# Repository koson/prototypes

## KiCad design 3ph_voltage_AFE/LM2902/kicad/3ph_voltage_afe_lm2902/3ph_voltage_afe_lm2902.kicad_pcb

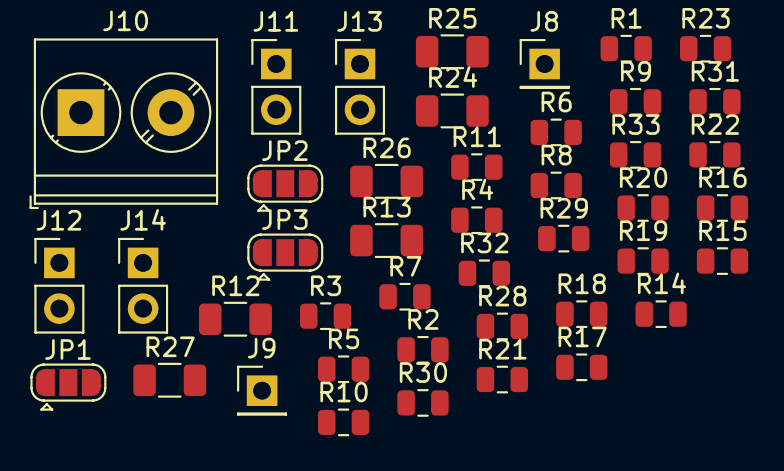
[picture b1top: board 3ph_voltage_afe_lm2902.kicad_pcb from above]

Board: 2 copper layers, 43 parts (0 on the bottom side), 29 nets, no tracks yet.

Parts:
J8: AC L; PinHeader_1x01_P2.54mm_Vertical
J9: AC N; PinHeader_1x01_P2.54mm_Vertical
J10: screw; TerminalBlock_Phoenix_PT-1,5-2-5.0-H_1x02_P5.00mm_Horizontal
J11: V_ref; PinHeader_1x02_P2.54mm_Vertical
J12: VDDA; PinHeader_1x02_P2.54mm_Vertical
J13: SIGNAL; PinHeader_1x02_P2.54mm_Vertical
J14: GNDA; PinHeader_1x02_P2.54mm_Vertical
JP1, JP2, JP3: Jumper_3_Bridged12; SolderJumper-3_P1.3mm_Open_RoundedPad1.0x1.5mm
R1, R2, R3, R4, R5, R6, R7, R8, R9, R15, R16, R17, R18, R19, R20, R21, R22, R23: 1M; R_0805_2012Metric
R10, R11, R28, R29, R30, R31: 240K; R_0805_2012Metric
R12, R13, R24, R25, R26, R27: R_div_ref; R_1206_3216Metric
R14, R32, R33: 15K; R_0805_2012Metric

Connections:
/AC_V_L: J8.1, J10.1, R1.1, R3.1, R4.1
/AC_V_N: J9.1, J10.2, R2.1, R5.1, R15.1
/GNDA: J14.1, J14.2, R13.1, R25.1, R27.1
/OUT_SIG: J13.1, J13.2, R14.2, R32.2, R33.2
/Reference_voltage: JP1.2, JP2.2, JP3.2, R10.2, R28.2, R30.2
/VDDA: J12.1, J12.2, R12.2, R24.2, R26.2
/V_div: JP1.1, JP2.1, JP3.1, R12.1, R13.2, R24.1, R25.2, R26.1, R27.2
/ext_ref: J11.1, J11.2, JP1.3, JP2.3, JP3.3
unnamed: R1.2, R16.1
unnamed: R4.2, R6.1
unnamed: R5.2, R7.1
unnamed: R6.2, R8.1
unnamed: R7.2, R9.1
unnamed: R8.2, R10.1
unnamed: R9.2, R11.1
unnamed: R11.2, R14.1
unnamed: R15.2, R19.1
unnamed: R16.2, R20.1
unnamed: R2.2, R17.1
unnamed: R17.2, R21.1
unnamed: R3.2, R18.1
unnamed: R18.2, R22.1
unnamed: R19.2, R23.1
unnamed: R20.2, R28.1
unnamed: R21.2, R29.1
unnamed: R22.2, R30.1
unnamed: R23.2, R31.1
unnamed: R29.2, R32.1
unnamed: R31.2, R33.1

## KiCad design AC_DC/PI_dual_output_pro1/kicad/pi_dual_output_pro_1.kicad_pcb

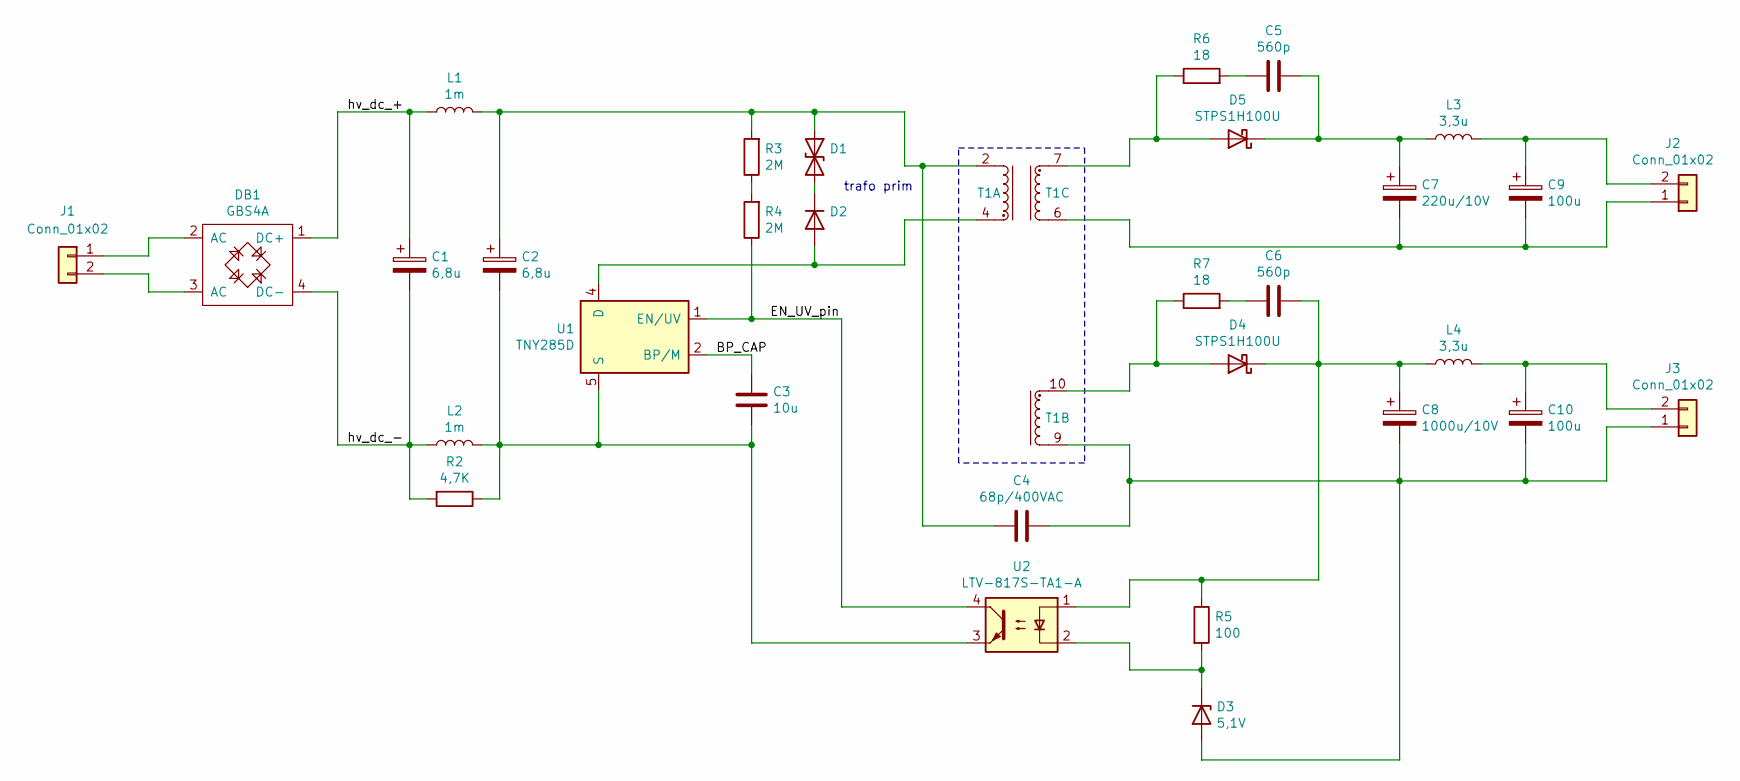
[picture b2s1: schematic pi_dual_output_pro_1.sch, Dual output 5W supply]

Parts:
C1, C2: 6,8u; CP_Radial_D10.0mm_P5.00mm
C3: 10u; C_0805_2012Metric
C4: 68p/400VAC; C_Disc_D5.0mm_W2.5mm_P5.00mm
C5, C6: 560p; C_0603_1608Metric
C7: 220u/10V; CP_Radial_D6.3mm_P2.50mm
C8: 1000u/10V; CP_Radial_D10.0mm_P5.00mm
C9, C10: 100u; CP_Radial_D5.0mm_P2.00mm
D1: SMAJ100A-13-F; D_SMA
D2: S1K; D_SMA
D3: 5,1V; D_SOD-123
D4, D5: STPS1H100U; D_SMB
DB1: GBS4A; Diode_Bridge_19.0x3.5x10.0mm_P5.0mm
J1, J2, J3: Conn_01x02; TerminalBlock_Phoenix_PT-1,5-2-5.0-H_1x02_P5.00mm_Horizontal
L1, L2: 1m; L_Radial_D8.7mm_P5.00mm_Fastron_07HCP
L3, L4: 3,3u; L_Radial_D6.0mm_P4.00mm
R2: 4,7K; R_0805_2012Metric
R3, R4: 2M; R_1206_3216Metric
R5: 100; R_0805_2012Metric
R6, R7: 18; R_0805_2012Metric
T1: EE13_Custom; EE13_Bobbin
U1: TNY285D; PowerIntegrations_SO-8C
U2: LTV-817S-TA1-A; SMDIP-4_W9.53mm

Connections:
/BP_CAP: C3.1, U1.2 (BP/M)
/EN_UV_pin: R4.1, U1.1 (EN/UV), U2.4
/hv_dc_+: C1.1, DB1.1 (DC+), L1.1
/hv_dc_-: C1.2, DB1.4 (DC-), L2.1, R2.2
unnamed: C2.1, C4.2, D1.1 (A1), L1.2, R3.2, T1.2
unnamed: C2.2, C3.2, L2.2, R2.1, U1.5 (S), U1.6 (S), U1.7 (S), U1.8 (S), U2.3
unnamed: C5.1, C7.1, D5.1 (K), L3.1
unnamed: C5.2, R6.2
unnamed: C6.1, C8.1, D4.1 (K), L4.1, R5.1, U2.1
unnamed: C6.2, R7.2
unnamed: C7.2, C9.2, J2.1, T1.6
unnamed: C9.1, J2.2, L3.2
unnamed: C10.1, J3.2, L4.2
unnamed: C4.1, C8.2, C10.2, D3.2 (A), J3.1, T1.9
unnamed: D1.2 (A2), D2.1 (K)
unnamed: D2.2 (A), T1.4, U1.4 (D)
unnamed: D3.1 (K), R5.2, U2.2
unnamed: D4.2 (A), R7.1, T1.10
unnamed: D5.2 (A), R6.1, T1.7
unnamed: DB1.2 (AC), J1.1
unnamed: DB1.3 (AC), J1.2
unnamed: R3.1, R4.2

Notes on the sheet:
trafo prim

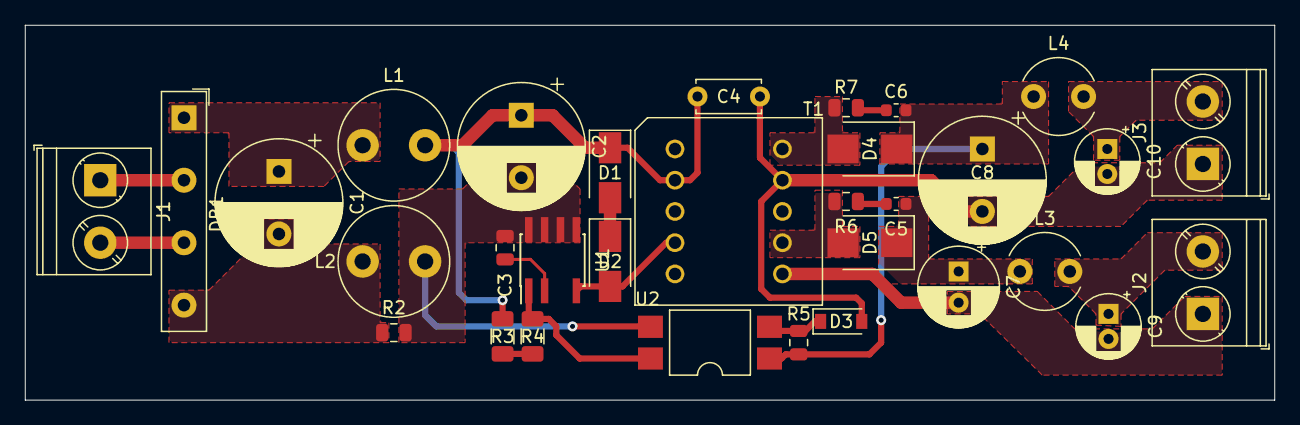
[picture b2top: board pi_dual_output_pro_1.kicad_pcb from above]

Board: 2 copper layers, 100.0 x 30.0 mm, 32 parts (0 on the bottom side), 22 nets.

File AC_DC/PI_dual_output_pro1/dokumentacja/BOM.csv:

Id;Oznaczenie;Obudowa;Iloæ;Oznaczenie;Dostawca;Numer artyku³u;PARKING / KOSZYK
1;R6,R7;R_0805_2012Metric;2;18;TME;0805S8J0180T5E;TAK
2;U2;SMDIP-4_W9.53mm;1;LTV-817S-TA1-A;TME; LTV-817S-TA1-B;TAK
3;DB1;Diode_Bridge_19.0x3.5x10.0mm_P5.0mm;1;GBS4A;TME; GBS4K ;TAK
4;T1;EE13_Bobbin;1;EE13_Custom;FERYSTER;TI-EE13-2X5V;-
6;C8;CP_Radial_D10.0mm_P5.00mm;1;1000u/10V;"TME
FARNELL";"ECA-1AHG102
EEUFS1A102";"TAK
TAK"
7;J3,J2,J1;TerminalBlock_Phoenix_PT-1,5-2-5.0-H_1x02_P5.00mm_Horizontal;3;Conn_01x02;-;-;-
8;D3;D_SOD-123;1;5,1V;TME;BZT52C5V1-13-F;TAK
9;D4,D5;D_SMB;1;STPS1H100U;TME;STPS1H100U;TAK
10;D2;D_SMA;1;S1K;TME;S1K;TAK
11;R4,R3;R_1206_3216Metric;2;2M;TME;1206S4J0205T5E;TAK
12;R5;R_0805_2012Metric;1;100;;;w zapasach
13;R2;R_0805_2012Metric;1;4,7K;;;w zapasach
14;L4,L3;L_Radial_D6.0mm_P4.00mm;2;3,3u;TME;COIL0608-0.0033;TAK
15;C4;C_Disc_D5.0mm_W2.5mm_P5.00mm;1;68p/400VAC;TME;CC-68/500;TAK
16;D1;D_SMA;1;P4SMA120A;TME;P4SMA120A;TAK
17;U1;PowerIntegrations_SO-8C;1;TNY285D;FARNELL;TNY285DG-TL;TAK
18;L2,L1;L_Radial_D8.7mm_P5.00mm_Fastron_07HCP;2;1m;TME;RLB0914-102KL;TAK
19;C10,C9;CP_Radial_D5.0mm_P2.00mm;2;100u;;;w zapasach
20;C7;CP_Radial_D6.3mm_P2.50mm;1;220u/10V;TME;EEUFC1A221SH;TAK
21;C6,C5;C_0603_1608Metric;2;560p;TME;0603B561K500CT;TAK
22;C3;C_0805_2012Metric;1;10u;TME;CL21A106KAYNNNG;TAK
23;C2,C1;CP_Radial_D10.0mm_P5.00mm;2;6,8u;TME;KJ2G6R8MNN1016;TAK

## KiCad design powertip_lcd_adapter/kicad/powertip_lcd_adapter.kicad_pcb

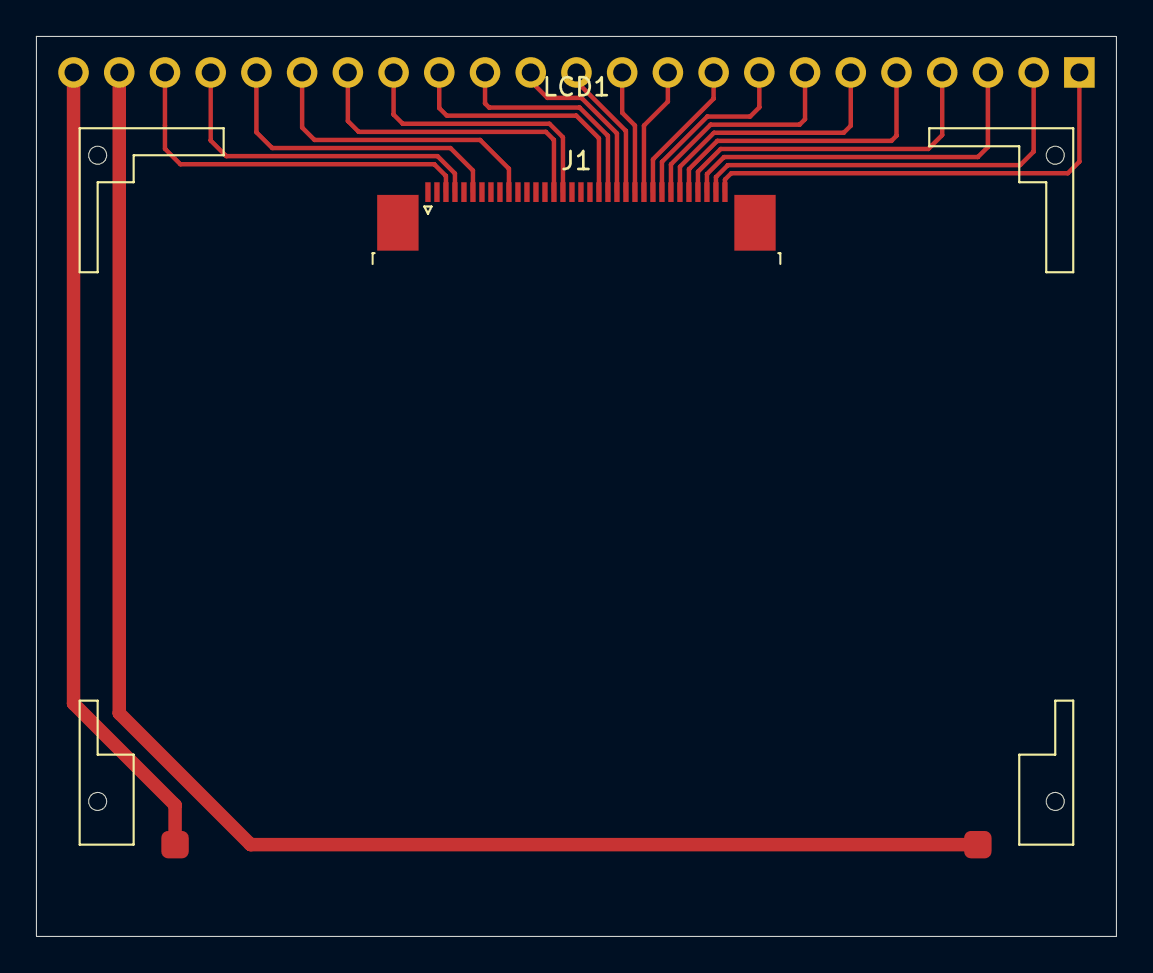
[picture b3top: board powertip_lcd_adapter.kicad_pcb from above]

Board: 2 copper layers, 60.0 x 50.0 mm, 3 parts (1 on the bottom side), 23 nets.

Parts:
J1: Conn_01x34; TE_3-1734839-4_1x34-1MP_P0.5mm_Horizontal
J2: Conn_01x23; PinHeader_1x23_P2.54mm_Vertical
LCD1: lcd_module; LCD_PE12864WRF-055-H-Q

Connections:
/A: J2.22, LCD1.2
/A_0: J1.32, J2.3
/C86: J1.4, J2.20
/CS_1: J1.34, J2.1
/D_0: J1.29, J2.6
/D_1: J1.28, J2.7
/D_2: J1.27, J2.8
/D_3: J1.26, J2.9
/D_4: J1.25, J2.10
/D_5: J1.24, J2.11
/D_6: J1.23, J2.12
/D_7: J1.22, J2.13
/K: J2.23, LCD1.1
/P_S: J1.3, J2.21
/RD: J1.30, J2.5
/RST: J1.33, J2.2
/VDD: J1.21, J2.14
/VG: J1.6, J2.19
/VM: J1.10, J2.18
/VSS: J1.20, J2.15
/V_0: J1.16, J2.16
/WR: J1.31, J2.4
/XV_0: J1.15, J2.17

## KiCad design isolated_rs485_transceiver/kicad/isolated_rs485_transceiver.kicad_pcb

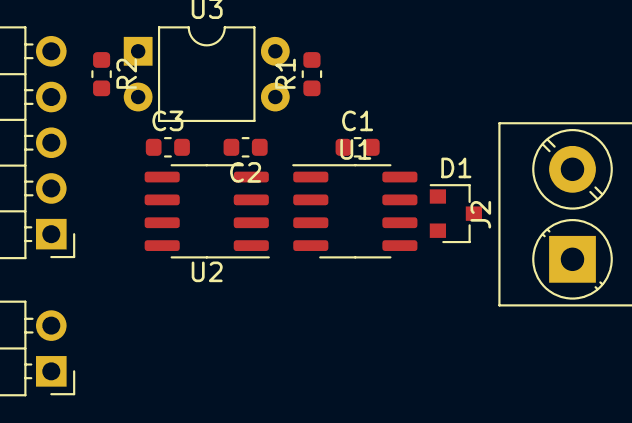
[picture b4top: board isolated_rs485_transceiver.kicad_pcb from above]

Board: 2 copper layers, 12 parts (0 on the bottom side), 13 nets, no tracks yet.

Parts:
C1, C2, C3: 100n; C_0603_1608Metric
D1: SM712_SOT23; SOT-23
J1: Conn_01x02; PinHeader_1x02_P2.54mm_Horizontal
J2: Conn_01x02; TerminalBlock_Phoenix_PT-1,5-2-5.0-H_1x02_P5.00mm_Horizontal
J3: Conn_01x05; PinHeader_1x05_P2.54mm_Horizontal
R1: 10K; R_0603_1608Metric
R2: 200; R_0603_1608Metric
U1: ST485EBDR; SOIC-8_3.9x4.9mm_P1.27mm
U2: FOD8012; SOIC-8_3.9x4.9mm_P1.27mm
U3: EL817; DIP-4_W7.62mm

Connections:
/Data_direction_HOST: J3.4, U3.2
/Data_direction_ISO: R1.2, U1.2, U1.3, U3.4
/GND_BUS: C1.1, C2.1, D1.3, J1.1, U1.5, U2.4, U3.3
/GND_HOST: C3.1, J3.5, U2.5
/RS485_A: D1.2, J2.1, U1.6
/RS485_B: D1.1, J2.2, U1.7
/RX_(out): J3.3, U2.6
/RX_(out)_iso: U1.1, U2.3
/TX_(in): J3.2, U2.7
/TX_(in)_iso: U1.4, U2.2
/VDD_BUS: C1.2, C2.2, J1.2, R1.1, U1.8, U2.1
/VDD_HOST: C3.2, J3.1, R2.2, U2.8
unnamed: R2.1, U3.1

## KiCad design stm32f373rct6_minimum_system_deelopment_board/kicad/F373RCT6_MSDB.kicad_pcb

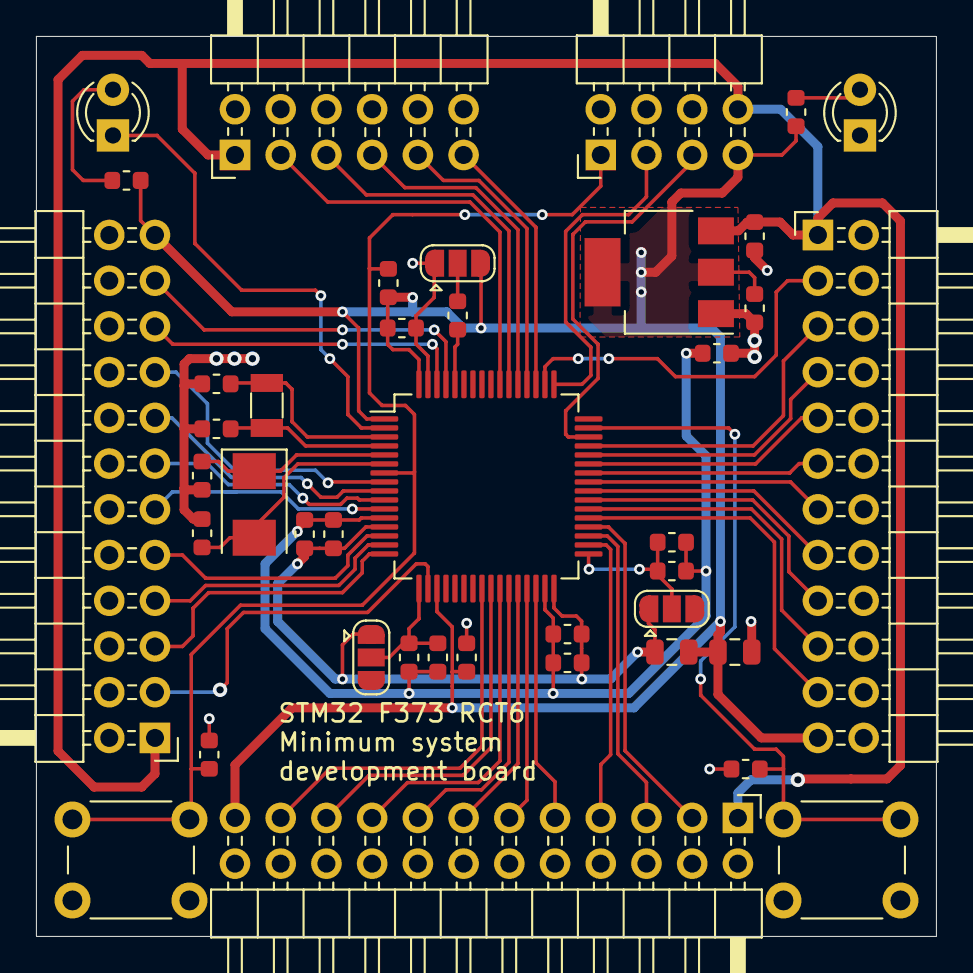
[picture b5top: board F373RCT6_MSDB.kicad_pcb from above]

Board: 2 copper layers, 50.0 x 50.0 mm, 41 parts (0 on the bottom side), 55 nets.

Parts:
C1, C8, C10, C12, C17: 10n; C_0603_1608Metric
C2, C3: 22p; C_0603_1608Metric
C4, C5: 12p; C_0603_1608Metric
C6, C9, C11, C13, C18: 1u; C_0603_1608Metric
C7, C14, C15, C19: 100n; C_0603_1608Metric
C16: 4,7u; C_0805_2012Metric
D1, D2: LED; LED_D3.0mm
J1: Conn_02x04_Odd_Even; PinHeader_2x04_P2.54mm_Horizontal
J2: Conn_02x06_Odd_Even; PinHeader_2x06_P2.54mm_Horizontal
J3, J4, J5: Conn_02x12_Odd_Even; PinHeader_2x12_P2.54mm_Horizontal
JP1: Jumper_VREFSD; SolderJumper-3_P1.3mm_Open_RoundedPad1.0x1.5mm
JP2: Jumper_VREF; SolderJumper-3_P1.3mm_Open_RoundedPad1.0x1.5mm
JP3: Jumper_BOOT0; SolderJumper-3_P1.3mm_Open_RoundedPad1.0x1.5mm
L1: 10u; L_0805_2012Metric
R1, R2: 10K; R_0603_1608Metric
R3: 0; R_0603_1608Metric
R4, R5: 510; R_0603_1608Metric
SW1: SW_RESET; SW_PUSH_6mm_H7.3mm
SW2: SW_F6; SW_PUSH_6mm_H7.3mm
U1: STM32F373RCTx; LQFP-64_10x10mm_P0.5mm
U2: LM1117-3.3; SOT-223-3_TabPin2
Y1: 8M; Crystal_SMD_5032-2Pin_5.0x3.2mm
Y2: 32768; Crystal_SMD_3215-2Pin_3.2x1.5mm

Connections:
+5V: C17.1, J1.8, J2.1, J3.1, J4.1, J5.1, U2.3
/A_0: J3.9, U1.14
/A_1: J3.7, U1.15
/A_2: J3.5, U1.16
/A_3: J3.3, U1.18
/A_8: J5.13, U1.41
/A_9: J5.11, U1.42
/A_10: J5.9, U1.43
/A_11: J5.7, U1.44
/A_12: J5.5, U1.45
/A_15: J5.3, U1.50
/B_0: J4.17, U1.26
/B_1: J4.15, U1.27
/B_2: J4.13, U1.28
/B_3: J2.3, U1.55
/B_8: J3.21, U1.61
/B_9: J3.19, U1.62
/B_14: J4.7, U1.34
/B_15: J4.5, U1.35
/C_0: J3.17, U1.8
/C_1: J3.15, U1.9
/C_2: J3.13, U1.10
/C_3: J3.11, U1.11
/C_4: J4.21, U1.24
/C_5: J4.19, U1.25
/C_6: J5.21, U1.37
/C_7: J5.19, U1.38
/C_8: J5.17, U1.39
/C_9: J5.15, U1.40
/C_10: J2.11, U1.51
/C_11: J2.9, U1.52
/C_12: J2.7, U1.53
/C_13: D1.1, U1.2
/D_2: J2.5, U1.54
/D_8: J4.3, U1.36
/E_8: J4.11, U1.29
/E_9: J4.9, U1.30
/F_6: C19.2, SW2.1, U1.47
/STM32F373RCT6/BOOT0: JP3.2, R1.1
/STM32F373RCT6/GNDA: C1.2, C6.2, C8.2, C9.2, C10.2, C11.2, C12.2, C13.2, R3.2, U1.12, U1.31
/STM32F373RCT6/VDDA: C1.1, C6.1, C8.1, C9.1, JP1.1, JP2.1, L1.1, U1.13, U1.32
/STM32F373RCT6/VREF+: C12.1, C13.1, JP2.2, U1.17
/STM32F373RCT6/VREFSD+: C10.1, C11.1, JP1.2, U1.33
/SWD_CLK: J1.3, U1.49
/SWD_DIO: J1.5, U1.46
/~uC_RESET: C7.2, J1.1, R2.1, SW1.1, U1.7
GND: C2.2, C3.2, C4.2, C5.2, C7.1, C14.2, C15.2, C16.2, C17.2, C18.2, C19.1, D2.1, J1.2, J1.4, J1.6, J2.2, J2.4, J2.6, J2.8, J2.10, J2.12, J3.2, J3.4, J3.6, J3.8, J3.10, J3.12, J3.14, J3.16, J3.18, J3.20, J3.22, J3.24, J4.2, J4.4, J4.6, J4.8, J4.10, J4.12, J4.14, J4.16, J4.18, J4.20, J4.22, J4.24, J5.2, J5.4, J5.6, J5.8, J5.10, J5.12, J5.14, J5.16, J5.18, J5.20, J5.22, J5.24, JP3.1, R3.1, SW1.2, SW2.2, U1.63, U2.1
unnamed: C2.1, U1.5, Y1.1
unnamed: C3.1, U1.6, Y1.2
unnamed: C4.1, U1.3, Y2.1
unnamed: C5.1, U1.4, Y2.2
unnamed: D1.2, R4.2
unnamed: D2.2, R5.2
unnamed: R1.2, U1.60
VDD: C14.1, C15.1, C16.1, C18.1, J1.7, J3.23, J4.23, J5.23, JP3.3, L1.2, R2.2, R4.1, R5.1, U1.1, U1.19, U1.64, U2.2

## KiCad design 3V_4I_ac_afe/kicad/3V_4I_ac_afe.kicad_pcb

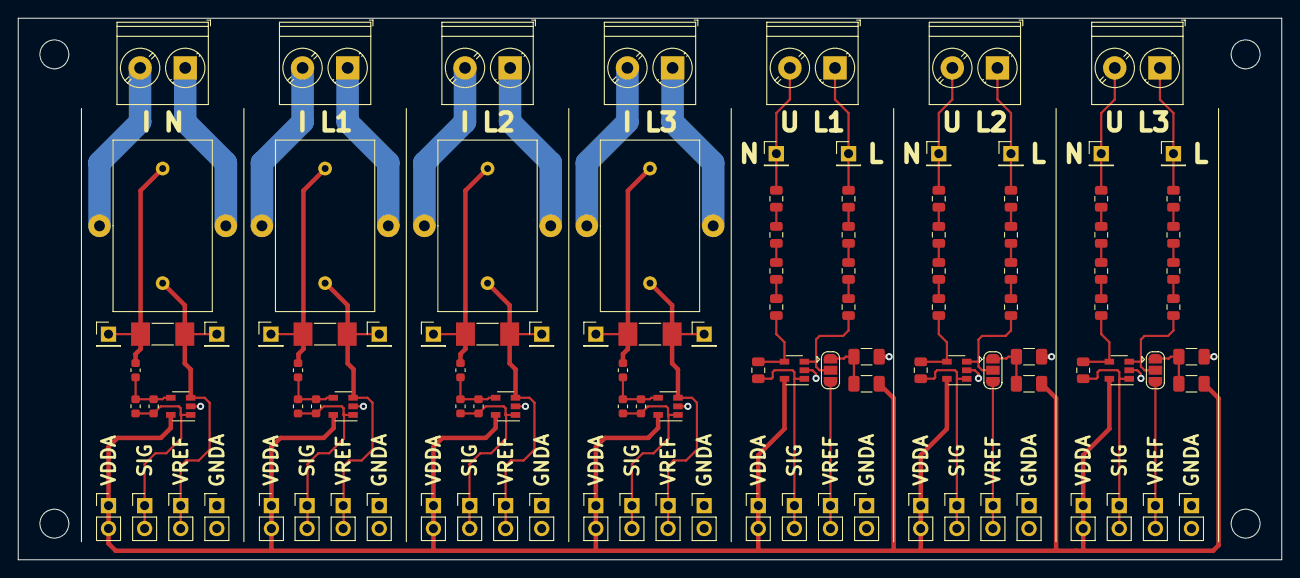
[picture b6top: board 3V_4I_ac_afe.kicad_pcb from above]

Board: 2 copper layers, 140.0 x 60.0 mm, 116 parts (0 on the bottom side), 65 nets.

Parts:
C1, C2, C3, C4: 4,7n; C_0603_1608Metric
CT1, CT2, CT3, CT4: Current_Transformer; CT_talema_pimary_wire
H1, H2, H3, H4: MountingHole; MountingHole_3.2mm_M3
J1, J10, J17, J24, J29, J36, J43: screw; TerminalBlock_Phoenix_PT-1,5-2-5.0-H_1x02_P5.00mm_Horizontal
J2, J3, J30, J31, J37, J38, J44, J45: CT_R; PinHeader_1x01_P2.54mm_Vertical
J4, J11, J18, J25, J32, J39, J46: V_ref; PinHeader_1x02_P2.54mm_Vertical
J5, J12, J19, J26, J33, J40, J47: VDDA; PinHeader_1x02_P2.54mm_Vertical
J6, J13, J20, J27, J34, J41, J48: SIGNAL; PinHeader_1x02_P2.54mm_Vertical
J7, J14, J21, J28, J35, J42, J49: GNDA; PinHeader_1x02_P2.54mm_Vertical
J8, J15, J22: AC L; PinHeader_1x01_P2.54mm_Vertical
J9, J16, J23: AC N; PinHeader_1x01_P2.54mm_Vertical
JP1, JP2, JP3: Jumper_3_Bridged12; SolderJumper-3_P1.3mm_Open_RoundedPad1.0x1.5mm
R1, R37, R40, R43: 10; R_MELF_MMB-0207
R2, R38, R41, R44: 1K; R_0603_1608Metric
R3, R39, R42, R45: 15K; R_0603_1608Metric
R4, R5, R6, R7, R8, R9, R15, R16, R17, R18, R19, R20, R26, R27, R28, R29, R30, R31: 1M; R_0805_2012Metric
R10, R11, R21, R22, R32, R33: 240K; R_0805_2012Metric
R12, R13, R23, R24, R34, R35: R_div_ref; R_1206_3216Metric
R14, R25, R36: 15K; R_0805_2012Metric
U1, U2, U3, U4, U5, U6, U7: MCP6021T; SOT-23-5

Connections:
/ac_i_afe_1/CT_coil: CT1.4, J2.1, R1.2, R2.2
/ac_i_afe_1/ext_ref: CT1.3, J3.1, J4.1, J4.2, R1.1, U1.3
/ac_i_afe_2/CT_coil: CT2.4, J30.1, R37.2, R38.2
/ac_i_afe_2/ext_ref: CT2.3, J31.1, J32.1, J32.2, R37.1, U5.3
/ac_i_afe_3/CT_coil: CT3.4, J37.1, R40.2, R41.2
/ac_i_afe_3/ext_ref: CT3.3, J38.1, J39.1, J39.2, R40.1, U6.3
/ac_i_afe_4/CT_coil: CT4.4, J44.1, R43.2, R44.2
/ac_i_afe_4/ext_ref: CT4.3, J45.1, J46.1, J46.2, R43.1, U7.3
/ac_v_afe_1/AC_V_L: J8.1, J10.1, R4.1
/ac_v_afe_1/AC_V_N: J9.1, J10.2, R5.1
/ac_v_afe_1/Reference_voltage: JP1.2, R10.2, U2.3
/ac_v_afe_1/V_div: JP1.1, R12.1, R13.2
/ac_v_afe_1/ext_ref: J11.1, J11.2, JP1.3
/ac_v_afe_2/AC_V_L: J15.1, J17.1, R15.1
/ac_v_afe_2/AC_V_N: J16.1, J17.2, R16.1
/ac_v_afe_2/Reference_voltage: JP2.2, R21.2, U3.3
/ac_v_afe_2/V_div: JP2.1, R23.1, R24.2
/ac_v_afe_2/ext_ref: J18.1, J18.2, JP2.3
/ac_v_afe_3/AC_V_L: J22.1, J24.1, R26.1
/ac_v_afe_3/AC_V_N: J23.1, J24.2, R27.1
/ac_v_afe_3/Reference_voltage: JP3.2, R32.2, U4.3
/ac_v_afe_3/V_div: JP3.1, R34.1, R35.2
/ac_v_afe_3/ext_ref: J25.1, J25.2, JP3.3
/signal_I1: C1.1, J6.1, J6.2, R3.1, U1.1
/signal_I2: C2.1, J34.1, J34.2, R39.1, U5.1
/signal_I3: C3.1, J41.1, J41.2, R42.1, U6.1
/signal_IN: C4.1, J48.1, J48.2, R45.1, U7.1
/signal_U1: J13.1, J13.2, R14.2, U2.1
/signal_U2: J20.1, J20.2, R25.2, U3.1
/signal_U3: J27.1, J27.2, R36.2, U4.1
GNDA: J7.1, J7.2, J14.1, J14.2, J21.1, J21.2, J28.1, J28.2, J35.1, J35.2, J42.1, J42.2, J49.1, J49.2, R13.1, R24.1, R35.1, U1.2, U2.2, U3.2, U4.2, U5.2, U6.2, U7.2
unnamed: C1.2, R2.1, R3.2, U1.4
unnamed: C2.2, R38.1, R39.2, U5.4
unnamed: C3.2, R41.1, R42.2, U6.4
unnamed: C4.2, R44.1, R45.2, U7.4
unnamed: CT1.1, J1.2
unnamed: CT1.2, J1.1
unnamed: CT2.1, J29.2
unnamed: CT2.2, J29.1
unnamed: CT3.1, J36.2
unnamed: CT3.2, J36.1
unnamed: CT4.1, J43.2
unnamed: CT4.2, J43.1
unnamed: R4.2, R6.1
unnamed: R5.2, R7.1
unnamed: R6.2, R8.1
unnamed: R7.2, R9.1
unnamed: R8.2, R10.1
unnamed: R9.2, R11.1
unnamed: R11.2, R14.1, U2.4
unnamed: R15.2, R17.1
unnamed: R16.2, R18.1
unnamed: R17.2, R19.1
unnamed: R18.2, R20.1
unnamed: R19.2, R21.1
unnamed: R20.2, R22.1
unnamed: R22.2, R25.1, U3.4
unnamed: R26.2, R28.1
unnamed: R27.2, R29.1
unnamed: R28.2, R30.1
unnamed: R29.2, R31.1
unnamed: R30.2, R32.1
unnamed: R31.2, R33.1
unnamed: R33.2, R36.1, U4.4
VDDA: J5.1, J5.2, J12.1, J12.2, J19.1, J19.2, J26.1, J26.2, J33.1, J33.2, J40.1, J40.2, J47.1, J47.2, R12.2, R23.2, R34.2, U1.5, U2.5, U3.5, U4.5, U5.5, U6.5, U7.5

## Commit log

2021-08-18 old repo copy
